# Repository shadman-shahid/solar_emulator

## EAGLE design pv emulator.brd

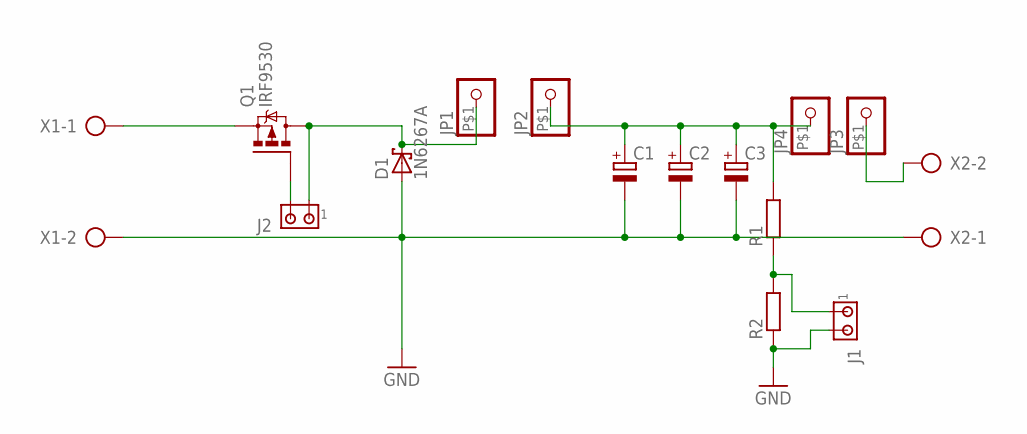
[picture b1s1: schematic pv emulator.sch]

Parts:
C1, C2, C3: CPOL-EUE5-10.5; E5-10,5
D1: 1N6267A; C4111-15
J1, J2: MTA02-100; 10X02MTA
JP1, JP2, JP3, JP4: PINHD-1X1-BIGPOGO; 1X1-BIGPOGO
Q1: IRF9530; TO220BV
R1, R2: R-EU_0204/7; 0204/7
X1, X2: AK300/2

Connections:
GND: C1.-, C2.-, C3.-, D1.A, J1.2, R2.1, X1.2, X2.1
unnamed: Q1.S, X1.1
unnamed: D1.C, J2.1, JP1.P$1, Q1.D
unnamed: C1.+, C2.+, C3.+, JP2.P$1, JP4.P$1, R1.2
unnamed: JP3.P$1, X2.2
unnamed: J1.1, R1.1, R2.2
unnamed: J2.2, Q1.G

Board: 2 copper layers, 15 parts (0 on the bottom side), 7 nets, no tracks yet.
